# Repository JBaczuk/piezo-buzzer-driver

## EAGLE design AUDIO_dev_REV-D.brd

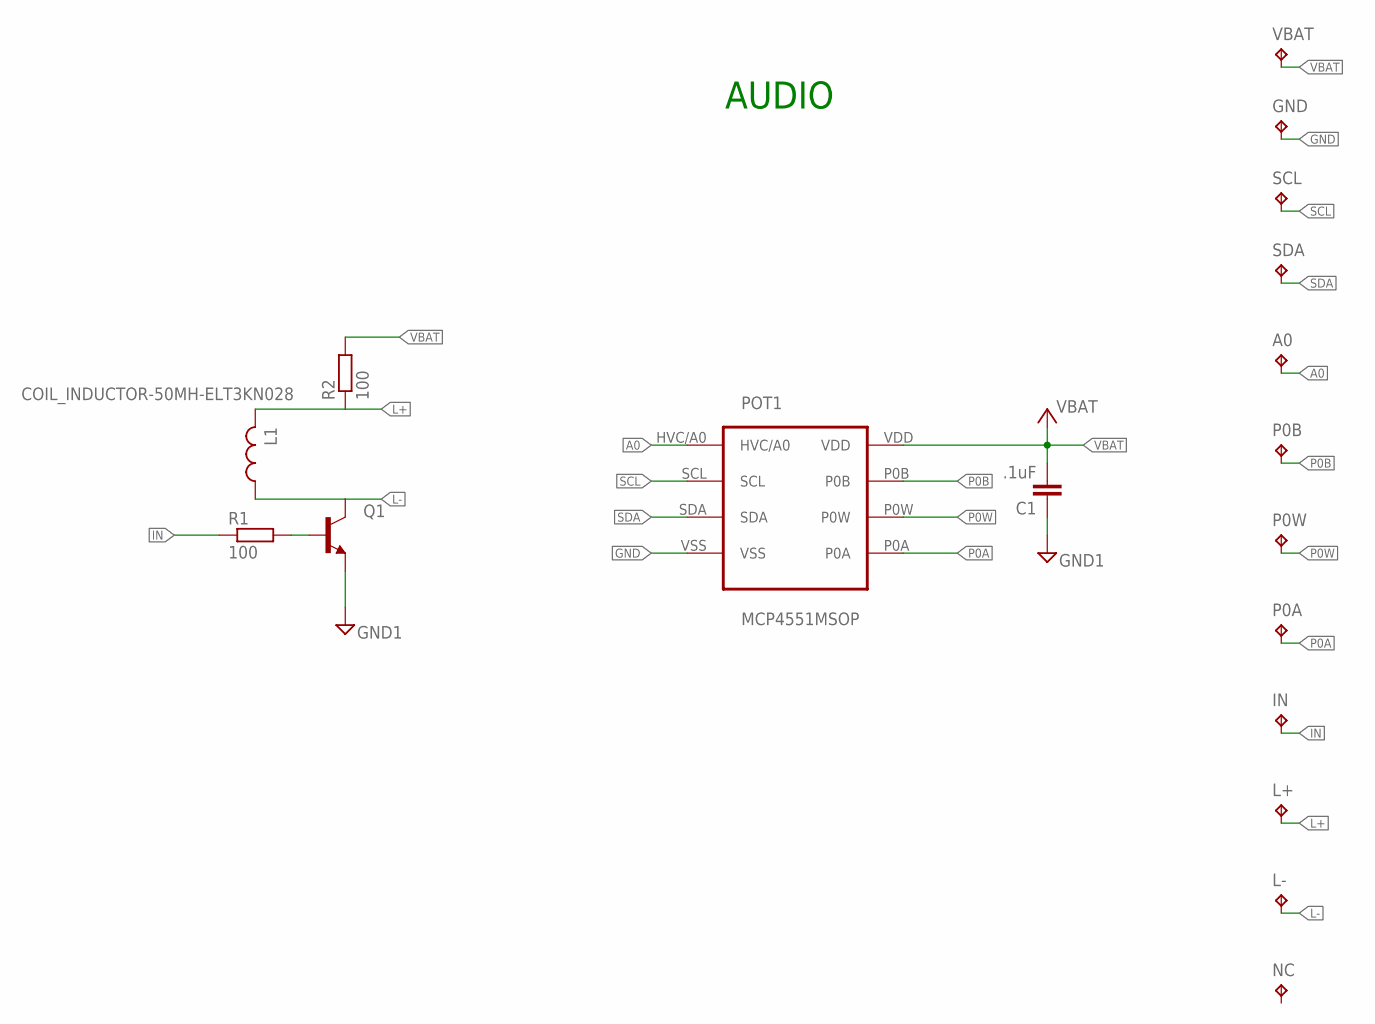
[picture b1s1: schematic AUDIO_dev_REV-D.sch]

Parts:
A0: 1X1_MALE_HEADER_0.1IN
C1: .1uF; 0603_PASSIVE
GND: 1X1_MALE_HEADER_0.1IN
IN: 1X1_MALE_HEADER_0.1IN
L1: COIL_INDUCTOR-50MH-ELT3KN028; ELT3KN028
L+: 1X1_MALE_HEADER_0.1IN
L-: 1X1_MALE_HEADER_0.1IN
NC: 1X1_MALE_HEADER_0.1IN
P0A, P0B, P0W: 1X1_MALE_HEADER_0.1IN
POT1: MCP4551MSOP; MCP4551-MSOP
Q1: NPN_SINGLE-BC846,215-SOT23-3; SOT23-3
R1, R2: 100; 0603_PASSIVE
SCL: 1X1_MALE_HEADER_0.1IN
SDA: 1X1_MALE_HEADER_0.1IN
VBAT: 1X1_MALE_HEADER_0.1IN

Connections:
A0: A0.P$8, POT1.HVC/A0
GND: C1.1, GND.P$8, POT1.VSS, Q1.E
IN: IN.P$8, R1.1
L+: L1.P$2 (2), L+.P$8, R2.1
L-: L1.P$1 (1), L-.P$8, Q1.C
unnamed: Q1.B, R1.2
P0A: P0A.P$8, POT1.P0A
P0B: P0B.P$8, POT1.P0B
P0W: P0W.P$8, POT1.P0W
SCL: POT1.SCL, SCL.P$8
SDA: POT1.SDA, SDA.P$8
VBAT: C1.2, POT1.VDD, R2.2, VBAT.P$8

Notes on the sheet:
AUDIO

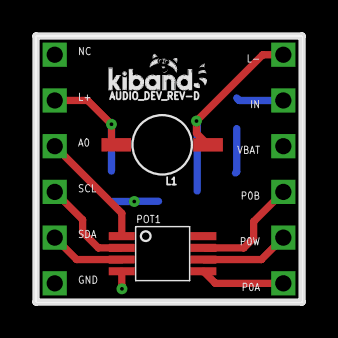
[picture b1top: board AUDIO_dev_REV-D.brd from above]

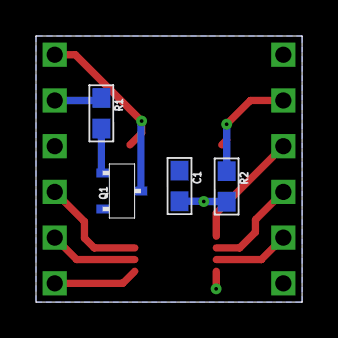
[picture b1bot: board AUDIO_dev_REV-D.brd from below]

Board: 2 copper layers, 14.8 x 14.8 mm, 18 parts (4 on the bottom side), 12 nets.

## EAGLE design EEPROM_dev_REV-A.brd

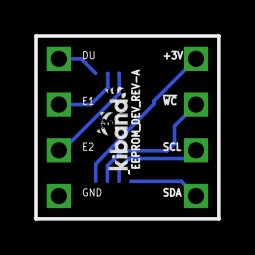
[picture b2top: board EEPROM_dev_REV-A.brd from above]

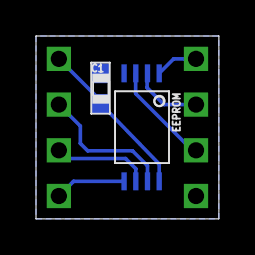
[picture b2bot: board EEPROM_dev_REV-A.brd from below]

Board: 2 copper layers, 10.2 x 10.2 mm, 10 parts (2 on the bottom side), 8 nets.

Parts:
!WC: 1X1_MALE_HEADER_0.1IN
+3V: 1X1_MALE_HEADER_0.1IN
C1: 0.1uF; 0603_PASSIVE
DU: 1X1_MALE_HEADER_0.1IN
E1, E2: 1X1_MALE_HEADER_0.1IN
EEPROM: M24M01_M24M018-SOIC; M24M01-RMN6TP
GND: 1X1_MALE_HEADER_0.1IN
SCL: 1X1_MALE_HEADER_0.1IN
SDA: 1X1_MALE_HEADER_0.1IN

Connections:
!WC: !WC.P$8, EEPROM.!WC
+3V: +3V.P$8, C1.1, EEPROM.VCC
DU: DU.P$8, EEPROM.DU
E1: E1.P$8, EEPROM.E1
E2: E2.P$8, EEPROM.E2
GND: C1.2, EEPROM.VSS, GND.P$8
SCL: EEPROM.SCL, SCL.P$8
SDA: EEPROM.SDA, SDA.P$8
